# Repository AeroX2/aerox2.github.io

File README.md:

# James Ridey's websites

One repository and npm installation builds the workshop at `jamesridey.dev`
and the professional site at `cv.jamesridey.dev`.

```sh
npm ci
npm run build
```

Outputs are `dist/workshop` and `dist/cv`. The build validates assets, résumé
consistency, and Cloudflare Pages limits. Run `npm run check` for Svelte and
TypeScript validation.

The workshop is an Astro site (`src/pages`) that prerenders the Svelte app to
static HTML, with one page per project at `/projects/<slug>`. Project data
lives in `src/data/projects.ts`. The CV is plain HTML built by
`vite.cv.config.ts`.

Use `npm run dev` for the workshop and `npm run dev:cv` for the CV. Use
`npm run preview` and `npm run preview:cv` to inspect production outputs.
Both websites get their PDF from `shared/James-Ridey-Resume.pdf`.

GitHub Actions builds both once and deploys the matching output to each
Cloudflare Pages project. Main pushes deploy both sites; pull requests only
build and validate. GitHub Pages deployments are removed; the old site must be unpublished in
repository Settings > Pages.

See [build and migration instructions](docs/professional-site.md) for account
setup, secrets, rollout, and rollback.

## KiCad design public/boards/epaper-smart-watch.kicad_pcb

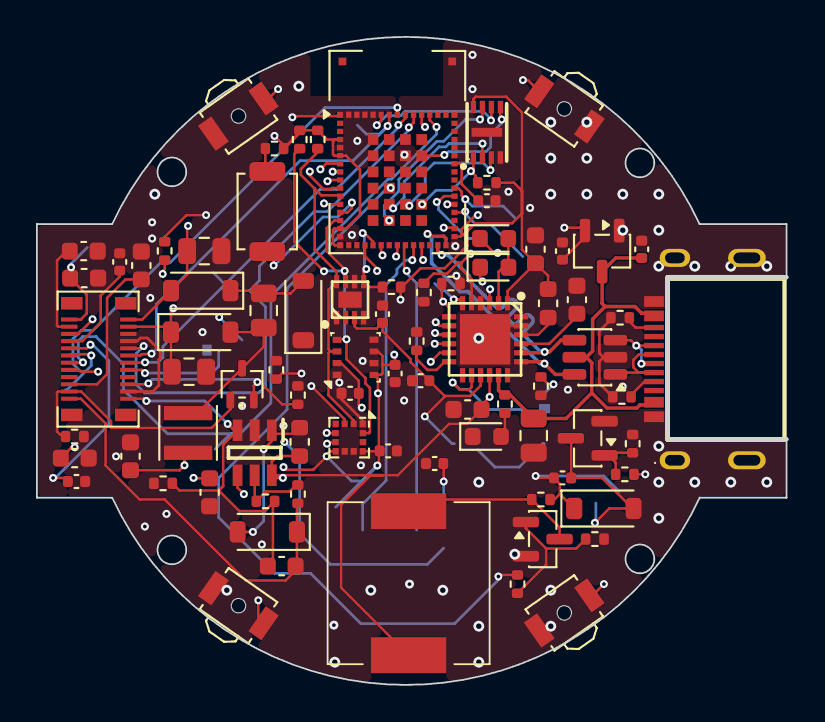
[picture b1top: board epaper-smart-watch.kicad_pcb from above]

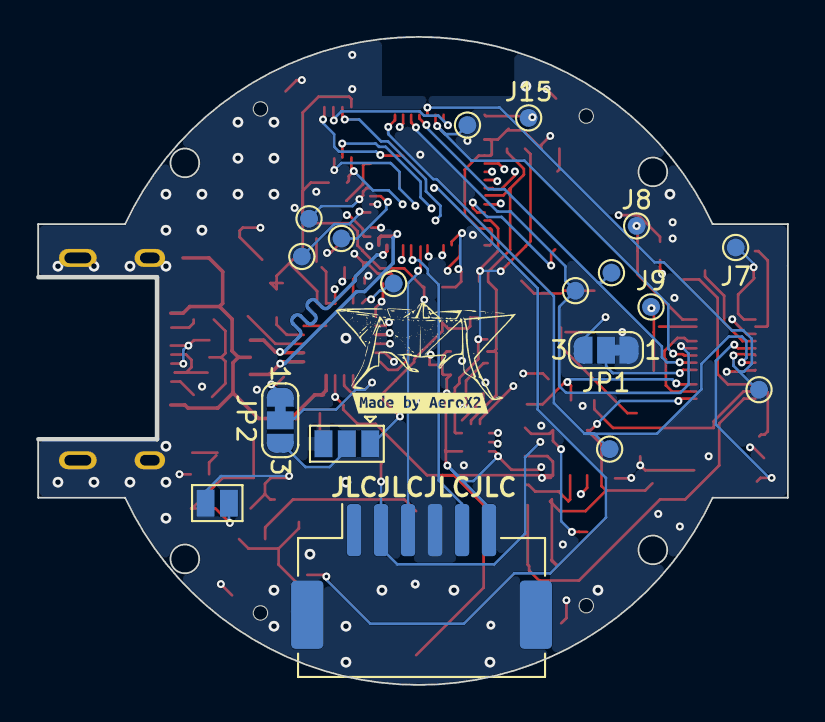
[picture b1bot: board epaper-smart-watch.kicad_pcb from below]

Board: 4 copper layers, 41.6 x 36.0 mm, 100 parts (19 on the bottom side), 78 nets.

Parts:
AC1: BMA400; LGA-12_2x2mm_P0.5mm
C2, C3, C4, C13, C22: 10uF/10V; C_0603_1608Metric
C5, C8, C18, C27: 1uF/25V; C_0402_1005Metric
C6, C9, C10, C11, C12, C24, C25, C26: 100nF/16V; C_0402_1005Metric
C7: 2.2uF/25V; C_0805_2012Metric
C14, C16, C19, C20: 1uF/50V; C_0603_1608Metric
C15, C23: 1uF/25V; C_0805_2012Metric
C17: 4.7uF/25V; C_0805_2012Metric
C21: 0.47uF/25V; C_0603_1608Metric
D1, D2, D3: LED; LED_0603_1608Metric
D5, D6, D7, D8, D9: MBR0530; D_SOD-123
IC2: NPM1100-QDAA-R7; QFN50P400X400X90-25N-D
IC3: MAX17048G+T10; SON50P200X200X80-9N-D
IC4: AP3032; SOT95P280X145-6N
J4, J7, J8, J9, J10, J11, J12, J13, J14, J15: TestPoint_Pad_D1.0mm
J5: Lithium Battery 3.7V; SolderJumper-3_P1.3mm_Open_Pad1.0x1.5mm
J6: AXT624124
J16: Touch3; TestPoint_Pad_D1.0mm
J17: Touch2; TestPoint_Pad_D1.0mm
J18: Touch1; TestPoint_Pad_D1.0mm
JP1, JP2: SolderJumper_3_Bridged12; SolderJumper-3_P1.3mm_Bridged12_RoundedPad1.0x1.5mm_NumberL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
L1: 2.2uH; L_0603_1608Metric
L2: NR3010T100M; L_Taiyo-Yuden_NR-30xx
L3: 6.8uH; L_0603_1608Metric
LS1: CPT-9019B-SMT-TR; CPT9019SSMTTR
M1: Motor_DC; SolderJumper-2_P1.3mm_Open_Pad1.0x1.5mm
P1: USB_C_Plug_USB2.0; USB-C-SMD_SHOU_TYPE-C-16P-CB1.6
Q2: Si1308EDL; SOT-323_SC-70
Q3, Q4: AO3400A; SOT-23
R1, R2, R16, R17, R18, R19: 10k; R_0402_1005Metric
R3, R4: 5.1k; R_0402_1005Metric
R5: 22k; R_0402_1005Metric
R6, R13, R21, R24: 1k; R_0402_1005Metric
R7, R15, R22: 100; R_0402_1005Metric
R8, R11, R12, R14, R20, R23: 100k; R_0402_1005Metric
R9: 0.47; R_0402_1005Metric
R10: 750k; R_0402_1005Metric
SW2, SW3, SW4, SW5: BTN; SW_SPST_B3U-3000P-B
SW6: SW_Push; SW_SPST_TS-1088-xR020
SWD1: JST-ZH6; JST_ZE_SM06B-ZESS-TB_1x06-1MP_P1.50mm_Horizontal
U1: BME280; Bosch_LGA-8_2.5x2.5mm_P0.65mm_ClockwisePinNumbering
U2: USBLC6-2SC6; SOT-23-6
U3: STM32WB5MMG; ST-SiP-LGA-86-11x7.3mm
U4: XT25F32FDTIGT; DFN-8_L3.0-W2.0-P0.50-BL-EP_XT25XXX
U5: XC6206P332MR; SOT-23-3
kibuzzard-6782824E: G***; kibuzzard-6782824E

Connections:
+3V0: AC1.3 (VDDIO), AC1.7 (VDD), AC1.10 (CSB), C2.1, C6.2, C11.1, C12.1, C13.1, C26.2, IC2.1 (VOUTB), J6.9, JP1.3 (B), L1.2, L2.1, R1.1, R2.1, R14.1, R17.1, R19.1, R21.1, SWD1.6, U1.2 (CSB), U1.6 (VDDIO), U1.8 (VDD), U3.4 (VREF), U3.6 (VDDA), U3.15 (VBAT), U3.17 (VDDSMPS), U4.8 (VCC)
+5V: C5.1, C7.1, IC2.17 (VBUS), P1.A4 (VBUS), P1.A9 (VBUS), P1.B4 (VBUS), P1.B9 (VBUS), R6.1, U2.5 (VBUS), U5.3 (VI)
/ACCL_INT1: AC1.5 (INT1), U3.12 (PC0)
/ACCL_INT2: AC1.6 (INT2), U3.9 (PC1)
/BATC_ALRT: IC3.5 (~ALRT), R17.2, U3.21 (PB3)
/BTN_1: SW2.1, U3.22 (PC10)
/BTN_2: SW3.2, U3.8 (PC2)
/BTN_3: SW4.1, U3.24 (PC12)
/BTN_4: SW5.1, U3.20 (PB4)
/CHGR_ISET: IC2.5 (ISET), R18.2, U3.33 (PD0)
/CHGR_MODE: IC2.7 (MODE), R13.2, U3.51 (PA9)
/CHGR_SHPHLD: IC2.11 (SHPHLD), U3.36 (PC6)
/D+: IC2.20 (D+), U2.4 (I/O2), U3.29 (PA12)
/D-: IC2.19 (D-), U2.6 (I/O1), U3.30 (PA11)
/EPD_BUSY: J6.15, J15.1 (Pin_1_1), U3.1 (PA2)
/EPD_CSB: J6.12, J12.1 (Pin_1_1), R19.2, U3.55 (PA4)
/EPD_DC: J6.13, J13.1 (Pin_1_1), U3.50 (PA8)
/EPD_GDR: J6.21, Q2.1 (G), R12.2
/EPD_LIGHT: IC4.4 (CTRL), R20.1, U3.7 (PC3)
/EPD_LIGHT_PWR_NEG: C16.2, IC4.3 (FB), J6.24, R11.2, R15.2
/EPD_LIGHT_PWR_POS: C16.1, D6.1 (K), J6.23, R10.1
/EPD_MOSI: J6.10, J10.1 (Pin_1_1), U3.52 (PA7)
/EPD_RESR: J6.20, Q2.2 (S), R9.2
/EPD_RST_N: J6.14, J14.1 (Pin_1_1), U3.53 (PA6)
/EPD_SPICL: J6.11, J11.1 (Pin_1_1), U3.54 (PA5)
/EPD_VCOM: C21.1, J6.1, J7.1 (Pin_1_1)
/EPD_VGH: C15.1, D5.1 (K), J6.4, J9.1 (Pin_1_1)
/EPD_VGL: C23.1, D8.2 (A), J6.2, J8.1 (Pin_1_1)
/FLASH_CLK: U3.56 (PA3), U4.6 (SCLK)
/FLASH_CS: R14.2, U3.70 (PD3), U4.1 (~CS)
/FLASH_IO0: U3.73 (PD4), U4.5 (SI(IO0))
/FLASH_IO1: U3.80 (PD5), U4.2 (SO(IO1))
/FLASH_IO2: U3.81 (PD6), U4.3 (WP#(IO2))
/FLASH_IO3: U3.67 (PD7), U4.7 (HOLD#(IO3))
/I2C_SCL: AC1.12 (SCX), IC3.7 (SCL), R2.2, U1.4 (SCK), U3.14 (PB8)
/I2C_SDA: AC1.2 (SDX), IC3.8 (SDA), R1.2, U1.3 (SDI), U3.11 (PB9)
/NRST: C24.2, SWD1.2, U3.10 (NRST)
/SND: R22.2, U3.79 (PE0)
/SWDCLK: SWD1.5, U3.26 (PA14)
/SWDIO: SWD1.3, U3.25 (PA13)
/VIB: R7.2, U3.27 (PA15)
/VSYS: C4.1, C9.1, C22.1, D1.2 (A), D2.2 (A), D9.1 (K), IC2.2 (VOUTBSET1), IC2.3 (VOUTBSET0), IC2.9 (VTERMSET), IC2.16 (VSYS), IC4.6 (VIN), L3.2, LS1.2, M1.1 (+), R24.1
/VUSB: C27.2, U3.32 (VDDUSB), U5.2 (VO)
GND: AC1.1 (SDO), AC1.8 (GNDIO), AC1.9 (GND), C2.2, C3.2, C4.2, C5.2, C6.1, C7.2, C8.2, C10.2, C11.2, C12.2, C13.2, C14.2, C15.2, C18.2, C19.2, C20.2, C21.2, C22.2, C23.2, C24.1, C25.2, C26.1, C27.1, D3.1 (K), D7.1 (K), IC2.4 (AVSS), IC2.23 (PVSS), IC2.25 (AVSS), IC3.1 (CTG), IC3.4 (GND), IC3.6 (QSTRT), IC3.9 (EP), IC4.2 (GND), J5.3, J6.8, J6.22, JP1.1 (A), P1.A1 (GND), P1.A12 (GND), P1.B1 (GND), P1.B12 (GND), P1.SH (SHIELD), Q3.2 (S), Q4.2 (S), R3.1, R4.1, R5.1, R8.2, R9.1, R12.1, R13.1, R15.1, R16.2, R18.1, R20.2, R23.2, SW2.2, SW3.1, SW4.2, SW5.2, SWD1.4, U1.1 (GND), U1.5 (SDO), U1.7 (GND), U2.2 (GND), U3.5 (VSS), U3.16 (VSSSMPS), U3.31 (VSS), U3.57 (VSS), U3.58 (ANT_IN), U3.59 (RF_OUT), U3.60 (VSS), U3.84 (VSS), U3.86 (VSS), U4.4 (VSS), U4.9 (EP), U5.1 (GND)
unnamed: D1.1 (K), IC2.10 (ERR)
unnamed: D2.1 (K), IC2.8 (CHG)
unnamed: D3.2 (A), R6.2
unnamed: C17.1, D5.2 (A), L2.2, Q2.3 (D)
unnamed: D6.2 (A), IC4.1 (SW), L3.1
unnamed: C17.2, D7.2 (A), D8.1 (K)
unnamed: C9.2, D9.2 (A), M1.2 (-), Q3.3 (D)
unnamed: C3.1, IC2.21 (DEC)
unnamed: IC2.12 (ICHG), R5.2
unnamed: IC2.14 (NTC), JP2.2 (C)
unnamed: IC2.6 (SHPACT), J4.1 (Pin_1_1)
unnamed: IC2.22 (SW), L1.1
unnamed: C8.1, C10.1, IC2.15 (VBAT), IC3.2 (CELL), IC3.3 (VDD), J5.1
unnamed: IC4.5 (OV), R10.2, R11.1
unnamed: J5.2, JP2.3 (B)
unnamed: C20.1, J6.3
unnamed: C19.1, J6.5
unnamed: C18.1, J6.7
unnamed: J6.16, JP1.2 (C)
unnamed: C14.1, J6.19
unnamed: J16.1 (Pin_1_1), U3.38 (PB15)
unnamed: J17.1 (Pin_1_1), U3.37 (PB14)
unnamed: J18.1 (Pin_1_1), U3.35 (PB13)
unnamed: JP2.1 (A), R16.1
unnamed: P1.A5 (CC1), R4.2
unnamed: P1.B5 (CC2), R3.2
unnamed: P1.A6 (D+), P1.B6 (D+), U2.3 (I/O2)
unnamed: P1.A7 (D-), P1.B7 (D-), U2.1 (I/O1)
unnamed: Q3.1 (G), R7.1, R8.1
unnamed: LS1.1, Q4.3 (D), R24.2
unnamed: Q4.1 (G), R22.1, R23.1
unnamed: R21.2, SW6.1
unnamed: C25.1, U3.41 (PB12)
unnamed: SW6.2, U3.13 (PH3-BOOT0)

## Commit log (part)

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2024-11-18 Initial commit for resume website
2024-11-19 Fix Roboto font, buzzwords ordering and buzzwords mobile
2024-11-19 Add experience section, other minor changes
2024-11-19 Add favicon, get site working
2024-11-21 Initial shader push
2024-11-21 lang="ts"
2024-11-21 Playing around with some small fixes
2024-11-22 Getting somewhere, maybe
2024-11-24 Temp commit
2024-11-25 Lets try the font flip trick
2024-11-25 Final SDF solution, I'm happy with
2026-01-06 Update content for 2026
2026-01-06 Change style of website entirely, going for more of a glass style. Update favicon to more represent me
2026-01-06 Add a typewritter effect and pentagon rotation animation
2026-01-06 Update Buzzwords to a features list
2026-01-06 Intersection observers to try and improve performance
2026-01-06 Introduce a scrambled text effect to the website
2026-01-06 Add a source code viewing mode
2026-01-06 Linting and formatting
2026-01-06 Make the SDF a little more interesting with a DNA twist animation and camera movements
2026-01-06 Fix light mode not initializing on startup
2026-01-06 Few little mobile tweaks
2026-01-06 Github icon dark mode fix Add a description about the SDF animation
2026-01-06 Add origami boat for SDF
